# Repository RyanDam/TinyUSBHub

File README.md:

# TinyUSBHub

Tiny USB Hub using GL850G or GL852G usb chipset

## Schematic

## Ordering PCB

Use `Production/TinyUSBHub_r0.1.zip` file to order PCB. Recommended PCB thickness is 1mm.

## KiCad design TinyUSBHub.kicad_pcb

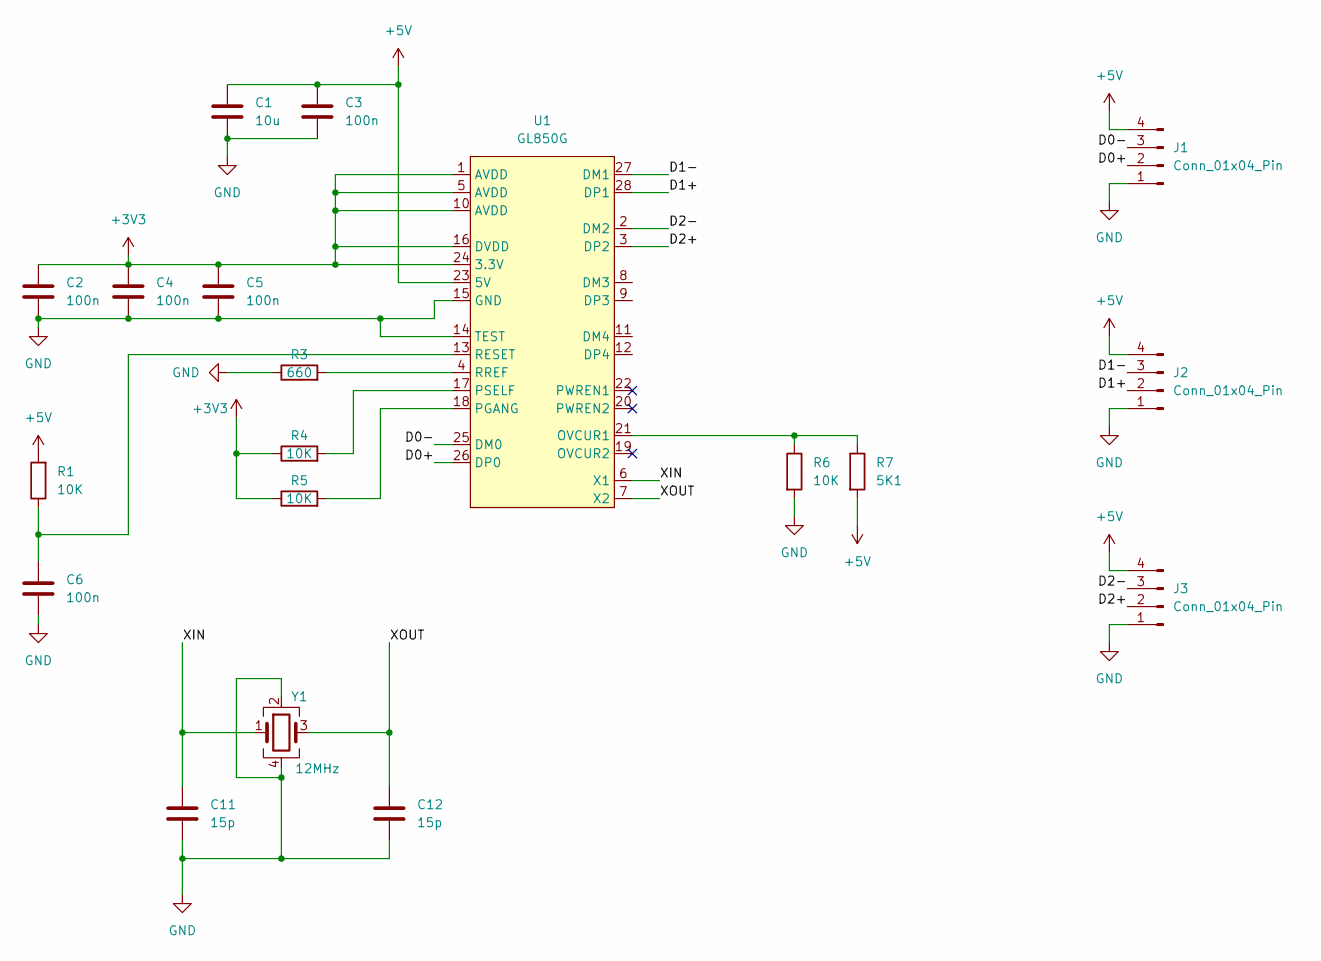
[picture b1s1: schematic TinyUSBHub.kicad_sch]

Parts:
C1: 10u; C_0603_1608Metric_Pad1.08x0.95mm_HandSolder
C2, C3, C4, C5, C6: 100n; C_0603_1608Metric_Pad1.08x0.95mm_HandSolder
C11, C12: 15p; C_0603_1608Metric_Pad1.08x0.95mm_HandSolder; LCSC_Part_Number C326803
J1, J2, J3: Conn_01x04_Pin; PinHeader_1x04_P2.00mm_Vertical
R1, R4, R5, R6: 10K; R_0603_1608Metric_Pad0.98x0.95mm_HandSolder
R3: 660; R_0603_1608Metric_Pad0.98x0.95mm_HandSolder
R7: 5K1; R_0603_1608Metric_Pad0.98x0.95mm_HandSolder
U1: GL850G; SSOP-28_5.3x10.2mm_P0.65mm
Y1: 12MHz; Crystal_SMD_3225-4Pin_3.2x2.5mm; LCSC_Part_Number C5765982

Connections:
+3V3: C2.1, C4.1, C5.1, R4.1, R5.1, U1.1 (AVDD), U1.5 (AVDD), U1.10 (AVDD), U1.16 (DVDD), U1.24 (3.3V)
+5V: C1.1, C3.1, J1.4, J2.4, J3.4, R1.2, R7.2, U1.23 (5V)
/D0+: J1.2, U1.26 (DP0)
/D0-: J1.3, U1.25 (DM0)
/D1+: J2.2, U1.28 (DP1)
/D1-: J2.3, U1.27 (DM1)
/D2+: J3.2, U1.3 (DP2)
/D2-: J3.3, U1.2 (DM2)
/XIN: C11.1, U1.6 (X1), Y1.1
/XOUT: C12.1, U1.7 (X2), Y1.3
GND: C1.2, C2.2, C3.2, C4.2, C5.2, C6.2, C11.2, C12.2, J1.1, J2.1, J3.1, R3.1, R6.2, U1.14 (TEST), U1.15 (GND), Y1.2, Y1.4
unnamed: R6.1, R7.1, U1.21 (OVCUR1)
unnamed: R5.2, U1.18 (PGANG)
unnamed: R4.2, U1.17 (PSELF)
unnamed: C6.1, R1.1, U1.13 (RESET)
unnamed: R3.2, U1.4 (RREF)

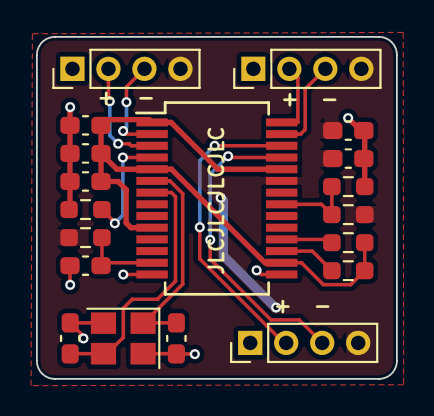
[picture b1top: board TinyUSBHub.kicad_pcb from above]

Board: 2 copper layers, 20.0 x 19.0 mm, 19 parts (0 on the bottom side), 16 nets.

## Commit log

2023-10-25 init commit
